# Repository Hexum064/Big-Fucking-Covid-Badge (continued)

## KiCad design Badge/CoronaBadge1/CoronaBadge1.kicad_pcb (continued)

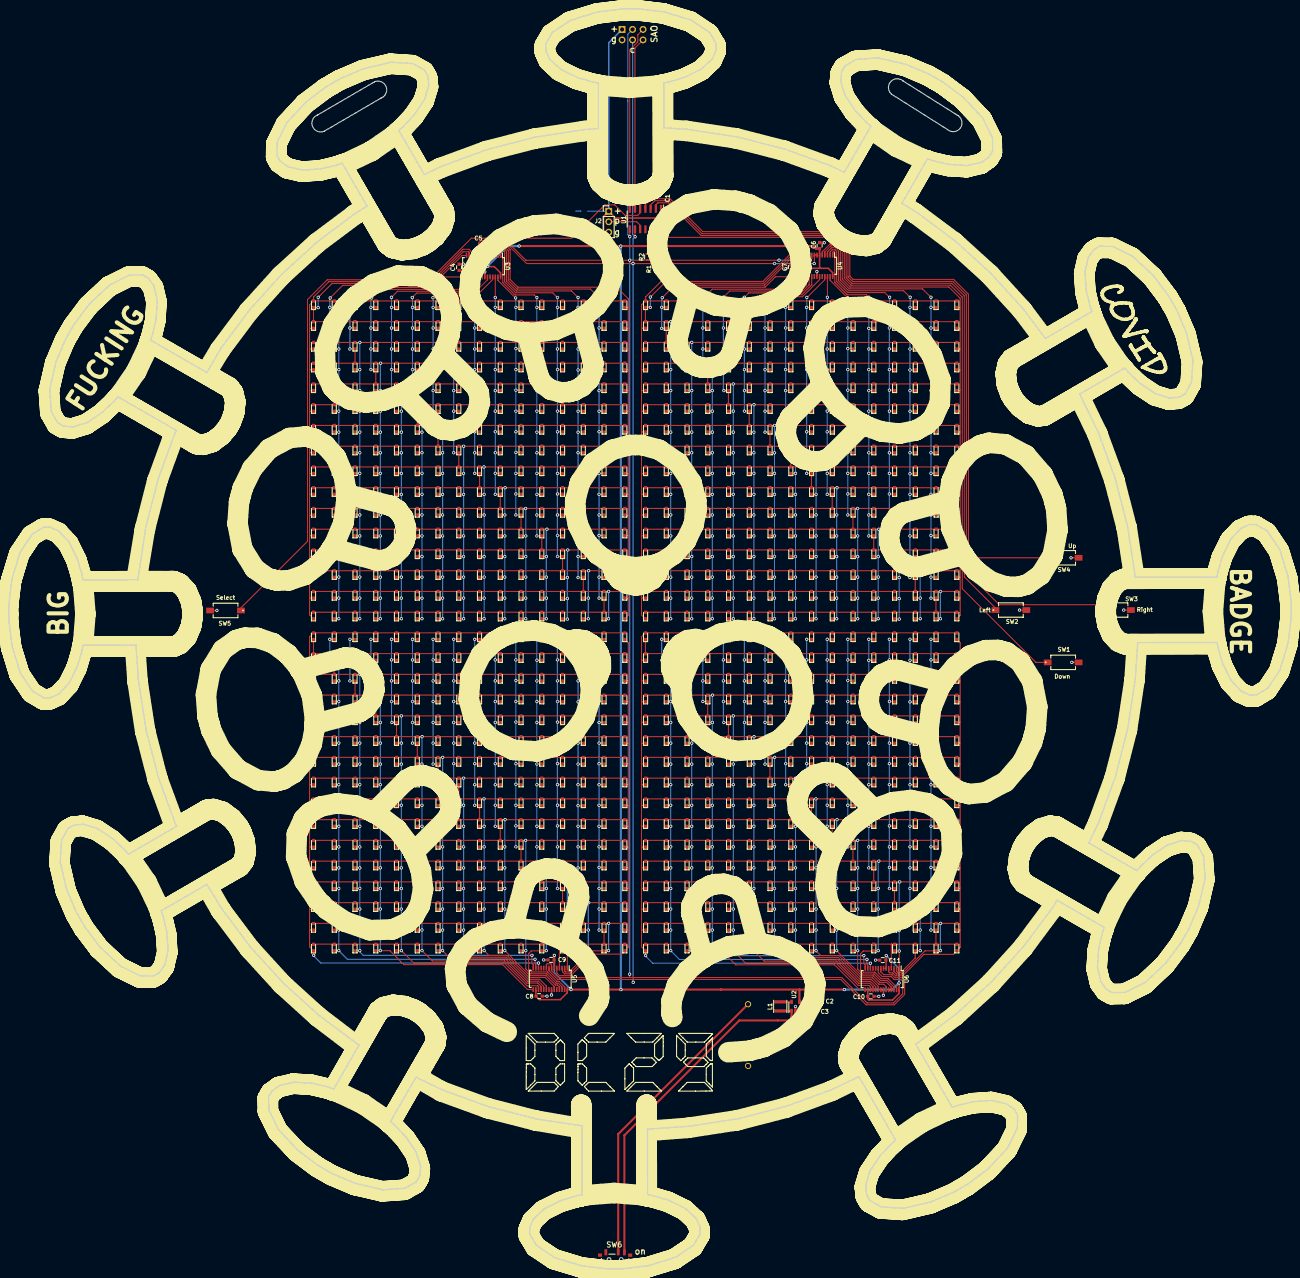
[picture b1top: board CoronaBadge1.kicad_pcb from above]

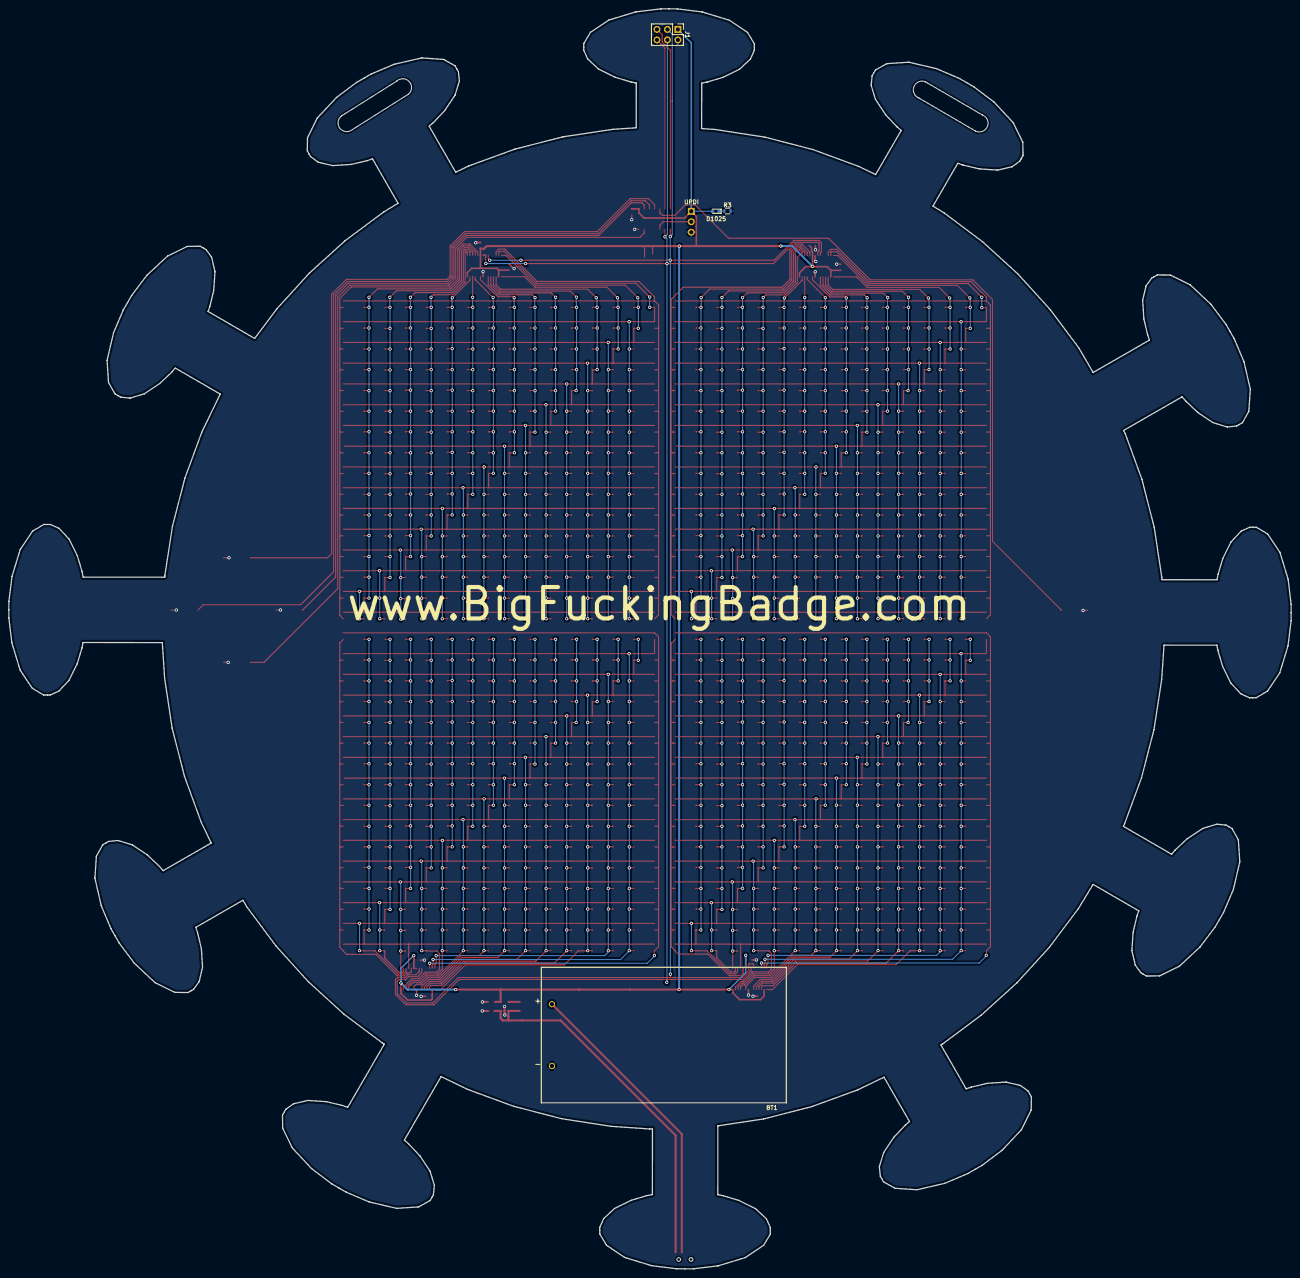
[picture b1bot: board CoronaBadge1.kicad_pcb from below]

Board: 2 copper layers, 311.4 x 306.0 mm, 1055 parts (4 on the bottom side), 84 nets.

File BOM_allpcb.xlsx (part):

*Ref Des | Manufacturer/Brand | *Mfg Part # | *Package | *Description / Value
D1 | https://lcsc.com/product-detail/Light-Emitting-Diodes-LED_XI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 | XL-1608SURC-06 | 0603 | 0603 SMT White LEDs
D2 | https://lcsc.com/product-detail/Light-Emitting-Diodes-LED_XI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 | XL-1608SURC-06 | 0603 | 0603 SMT White LEDs
D3 | https://lcsc.com/product-detail/Light-Emitting-Diodes-LED_XI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 | XL-1608SURC-06 | 0603 | 603 SMT White LEDs
D4 | https://lcsc.com/product-detail/Light-Emitting-Diodes-LED_XI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 | XL-1608SURC-06 | 0603 | 603 SMT White LEDs
D5 | https://lcsc.com/product-detail/Light-Emitting-Diodes-LED_XI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 | XL-1608SURC-06 | 0603 | 603 SMT White LEDs
D6 | https://lcsc.com/product-detail/Light-Emitting-Diodes-LED_XI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 | XL-1608SURC-06 | 0603 | 603 SMT White LEDs
D7 | https://lcsc.com/product-detail/Light-Emitting-Diodes-LED_XI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 | XL-1608SURC-06 | 0603 | 603 SMT White LEDs
D8 | https://lcsc.com/product-detail/Light-Emitting-Diodes-LED_XI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 | XL-1608SURC-06 | 0603 | 603 SMT White LEDs
D9 | https://lcsc.com/product-detail/Light-Emitting-Diodes-LED_XI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 | XL-1608SURC-06 | 0603 | 603 SMT White LEDs
D10 | https://lcsc.com/product-detail/Light-Emitting-Diodes-LED_XI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 | XL-1608SURC-06 | 0603 | 603 SMT White LEDs
D11 | https://lcsc.com/product-detail/Light-Emitting-Diodes-LED_XI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 | XL-1608SURC-06 | 0603 | 603 SMT White LEDs
D12 | https://lcsc.com/product-detail/Light-Emitting-Diodes-LED_XI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 | XL-1608SURC-06 | 0603 | 603 SMT White LEDs
D13 | https://lcsc.com/product-detail/Light-Emitting-Diodes-LED_XI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 | XL-1608SURC-06 | 0603 | 603 SMT White LEDs
D14 | https://lcsc.com/product-detail/Light-Emitting-Diodes-LED_XI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 | XL-1608SURC-06 | 0603 | 603 SMT White LEDs
D15 | https://lcsc.com/product-detail/Light-Emitting-Diodes-LED_XI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 | XL-1608SURC-06 | 0603 | 603 SMT White LEDs
D16 | https://lcsc.com/product-detail/Light-Emitting-Diodes-LED_XI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 | XL-1608SURC-06 | 0603 | 603 SMT White LEDs
D17 | https://lcsc.com/product-detail/Light-Emitting-Diodes-LED_XI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 | XL-1608SURC-06 | 0603 | 603 SMT White LEDs
D18 | https://lcsc.com/product-detail/Light-Emitting-Diodes-LED_XI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 | XL-1608SURC-06 | 0603 | 603 SMT White LEDs
D19 | https://lcsc.com/product-detail/Light-Emitting-Diodes-LED_XI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 | XL-1608SURC-06 | 0603 | 603 SMT White LEDs
D20 | https://lcsc.com/product-detail/Light-Emitting-Diodes-LED_XI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 | XL-1608SURC-06 | 0603 | 603 SMT White LEDs
D21 | https://lcsc.com/product-detail/Light-Emitting-Diodes-LED_XI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 | XL-1608SURC-06 | 0603 | 603 SMT White LEDs
D22 | https://lcsc.com/product-detail/Light-Emitting-Diodes-LED_XI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 | XL-1608SURC-06 | 0603 | 603 SMT White LEDs
D23 | https://lcsc.com/product-detail/Light-Emitting-Diodes-LED_XI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 | XL-1608SURC-06 | 0603 | 603 SMT White LEDs
D24 | https://lcsc.com/product-detail/Light-Emitting-Diodes-LED_XI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 | XL-1608SURC-06 | 0603 | 603 SMT White LEDs
D25 | https://lcsc.com/product-detail/Light-Emitting-Diodes-LED_XI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 | XL-1608SURC-06 | 0603 | 603 SMT White LEDs
D26 | https://lcsc.com/product-detail/Light-Emitting-Diodes-LED_XI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 | XL-1608SURC-06 | 0603 | 603 SMT White LEDs
D27 | https://lcsc.com/product-detail/Light-Emitting-Diodes-LED_XI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 | XL-1608SURC-06 | 0603 | 603 SMT White LEDs
D28 | https://lcsc.com/product-detail/Light-Emitting-Diodes-LED_XI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 | XL-1608SURC-06 | 0603 | 603 SMT White LEDs
D29 | https://lcsc.com/product-detail/Light-Emitting-Diodes-LED_XI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 | XL-1608SURC-06 | 0603 | 603 SMT White LEDs
D30 | https://lcsc.com/product-detail/Light-Emitting-Diodes-LED_XI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 | XL-1608SURC-06 | 0603 | 603 SMT White LEDs
D31 | https://lcsc.com/product-detail/Light-Emitting-Diodes-LED_XI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 | XL-1608SURC-06 | 0603 | 603 SMT White LEDs
D32 | https://lcsc.com/product-detail/Light-Emitting-Diodes-LED_XI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 | XL-1608SURC-06 | 0603 | 603 SMT White LEDs
D33 | https://lcsc.com/product-detail/Light-Emitting-Diodes-LED_XI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 | XL-1608SURC-06 | 0603 | 603 SMT White LEDs
D34 | https://lcsc.com/product-detail/Light-Emitting-Diodes-LED_XI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 | XL-1608SURC-06 | 0603 | 603 SMT White LEDs
D35 | https://lcsc.com/product-detail/Light-Emitting-Diodes-LED_XI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 | XL-1608SURC-06 | 0603 | 603 SMT White LEDs
D36 | https://lcsc.com/product-detail/Light-Emitting-Diodes-LED_XI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 | XL-1608SURC-06 | 0603 | 603 SMT White LEDs
D37 | https://lcsc.com/product-detail/Light-Emitting-Diodes-LED_XI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 | XL-1608SURC-06 | 0603 | 603 SMT White LEDs
D38 | https://lcsc.com/product-detail/Light-Emitting-Diodes-LED_XI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 | XL-1608SURC-06 | 0603 | 603 SMT White LEDs
D39 | https://lcsc.com/product-detail/Light-Emitting-Diodes-LED_XI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 | XL-1608SURC-06 | 0603 | 603 SMT White LEDs
D40 | https://lcsc.com/product-detail/Light-Emitting-Diodes-LED_XI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 | XL-1608SURC-06 | 0603 | 603 SMT White LEDs
D41 | https://lcsc.com/product-detail/Light-Emitting-Diodes-LED_XI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 | XL-1608SURC-06 | 0603 | 603 SMT White LEDs
D42 | https://lcsc.com/product-detail/Light-Emitting-Diodes-LED_XI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 | XL-1608SURC-06 | 0603 | 603 SMT White LEDs
D43 | https://lcsc.com/product-detail/Light-Emitting-Diodes-LED_XI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 | XL-1608SURC-06 | 0603 | 603 SMT White LEDs
D44 | https://lcsc.com/product-detail/Light-Emitting-Diodes-LED_XI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 | XL-1608SURC-06 | 0603 | 603 SMT White LEDs
D45 | https://lcsc.com/product-detail/Light-Emitting-Diodes-LED_XI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 | XL-1608SURC-06 | 0603 | 603 SMT White LEDs
D46 | https://lcsc.com/product-detail/Light-Emitting-Diodes-LED_XI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 | XL-1608SURC-06 | 0603 | 603 SMT White LEDs
D47 | https://lcsc.com/product-detail/Light-Emitting-Diodes-LED_XI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 | XL-1608SURC-06 | 0603 | 603 SMT White LEDs
D48 | https://lcsc.com/product-detail/Light-Emitting-Diodes-LED_XI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 | XL-1608SURC-06 | 0603 | 603 SMT White LEDs
D49 | https://lcsc.com/product-detail/Light-Emitting-Diodes-LED_XI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 | XL-1608SURC-06 | 0603 | 603 SMT White LEDs
D50 | https://lcsc.com/product-detail/Light-Emitting-Diodes-LED_XI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 | XL-1608SURC-06 | 0603 | 603 SMT White LEDs
D51 | https://lcsc.com/product-detail/Light-Emitting-Diodes-LED_XI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 | XL-1608SURC-06 | 0603 | 603 SMT White LEDs
D52 | https://lcsc.com/product-detail/Light-Emitting-Diodes-LED_XI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 | XL-1608SURC-06 | 0603 | 603 SMT White LEDs
D53 | https://lcsc.com/product-detail/Light-Emitting-Diodes-LED_XI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 | XL-1608SURC-06 | 0603 | 603 SMT White LEDs
D54 | https://lcsc.com/product-detail/Light-Emitting-Diodes-LED_XI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 | XL-1608SURC-06 | 0603 | 603 SMT White LEDs
D55 | https://lcsc.com/product-detail/Light-Emitting-Diodes-LED_XI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 | XL-1608SURC-06 | 0603 | 603 SMT White LEDs
D56 | https://lcsc.com/product-detail/Light-Emitting-Diodes-LED_XI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 | XL-1608SURC-06 | 0603 | 603 SMT White LEDs
D57 | https://lcsc.com/product-detail/Light-Emitting-Diodes-LED_XI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 | XL-1608SURC-06 | 0603 | 603 SMT White LEDs
D58 | https://lcsc.com/product-detail/Light-Emitting-Diodes-LED_XI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 | XL-1608SURC-06 | 0603 | 603 SMT White LEDs
D59 | https://lcsc.com/product-detail/Light-Emitting-Diodes-LED_XI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 | XL-1608SURC-06 | 0603 | 603 SMT White LEDs
D60 | https://lcsc.com/product-detail/Light-Emitting-Diodes-LED_XI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 | XL-1608SURC-06 | 0603 | 603 SMT White LEDs
D61 | https://lcsc.com/product-detail/Light-Emitting-Diodes-LED_XI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 | XL-1608SURC-06 | 0603 | 603 SMT White LEDs
D62 | https://lcsc.com/product-detail/Light-Emitting-Diodes-LED_XI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 | XL-1608SURC-06 | 0603 | 603 SMT White LEDs
D63 | https://lcsc.com/product-detail/Light-Emitting-Diodes-LED_XI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 | XL-1608SURC-06 | 0603 | 603 SMT White LEDs
D64 | https://lcsc.com/product-detail/Light-Emitting-Diodes-LED_XI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 | XL-1608SURC-06 | 0603 | 603 SMT White LEDs
D65 | https://lcsc.com/product-detail/Light-Emitting-Diodes-LED_XI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 | XL-1608SURC-06 | 0603 | 603 SMT White LEDs
D66 | https://lcsc.com/product-detail/Light-Emitting-Diodes-LED_XI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 | XL-1608SURC-06 | 0603 | 603 SMT White LEDs
D67 | https://lcsc.com/product-detail/Light-Emitting-Diodes-LED_XI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 | XL-1608SURC-06 | 0603 | 603 SMT White LEDs
D68 | https://lcsc.com/product-detail/Light-Emitting-Diodes-LED_XI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 | XL-1608SURC-06 | 0603 | 603 SMT White LEDs
D69 | https://lcsc.com/product-detail/Light-Emitting-Diodes-LED_XI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 | XL-1608SURC-06 | 0603 | 603 SMT White LEDs
D70 | https://lcsc.com/product-detail/Light-Emitting-Diodes-LED_XI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 | XL-1608SURC-06 | 0603 | 603 SMT White LEDs
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
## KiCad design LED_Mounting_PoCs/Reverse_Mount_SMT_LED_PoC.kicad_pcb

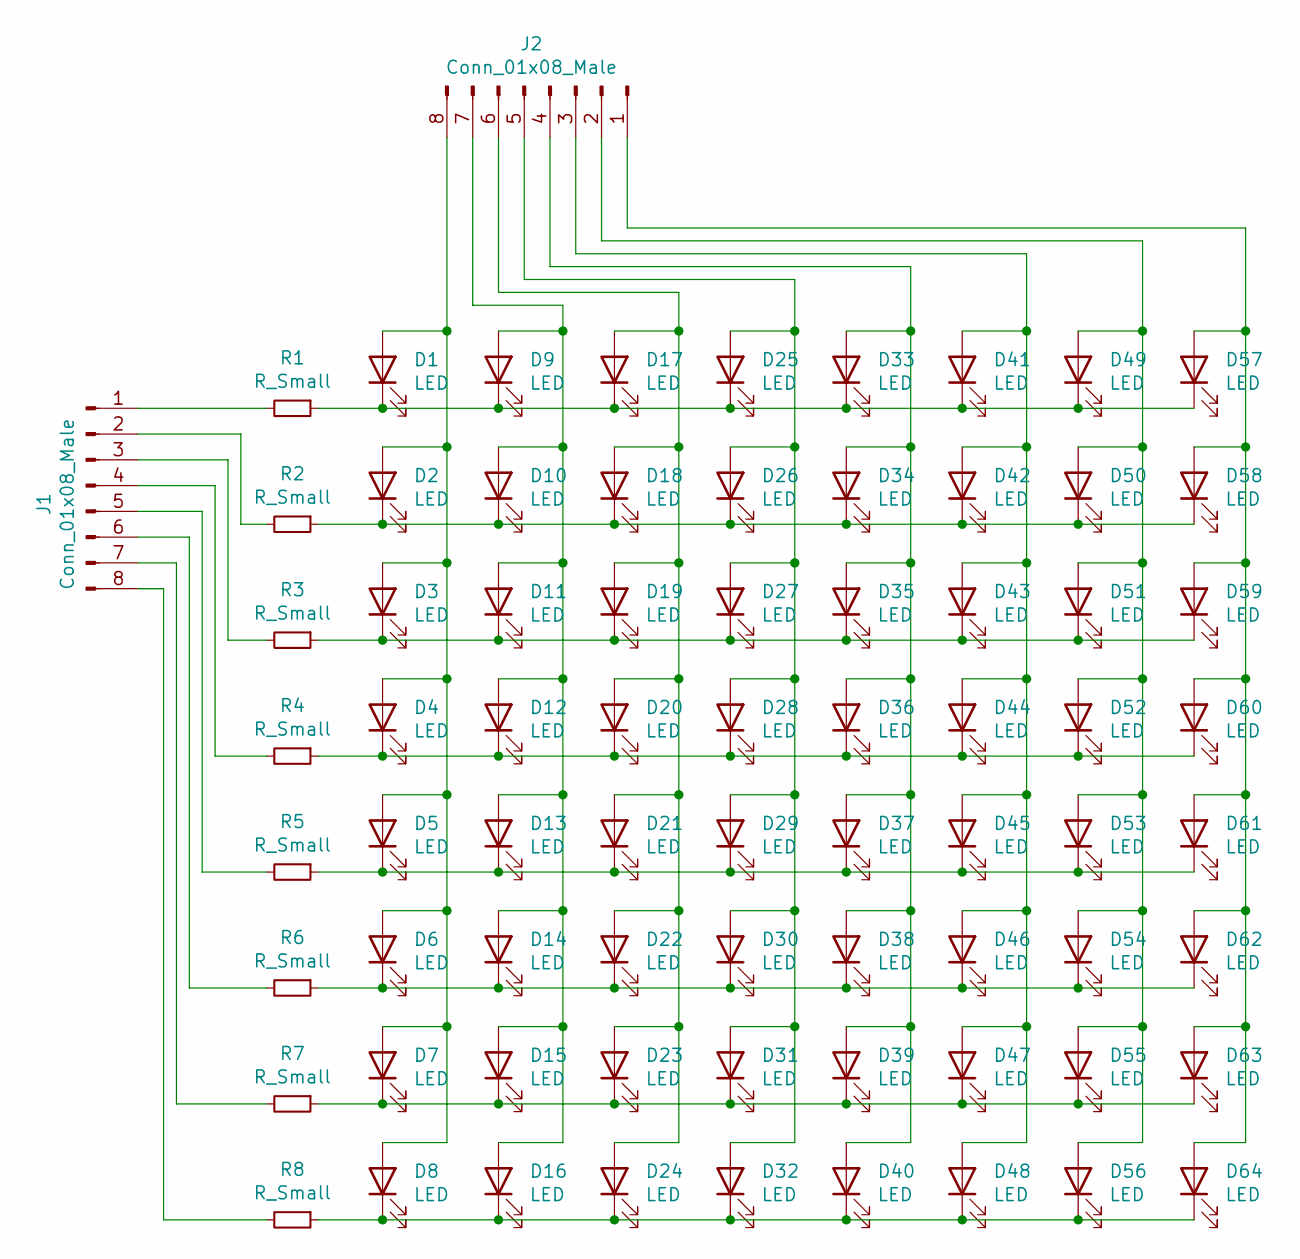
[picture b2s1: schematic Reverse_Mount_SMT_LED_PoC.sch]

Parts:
D1, D2, D3, D4, D5, D6, D7, D8, D9, D10, D11, D12, D13, D14, D15, D16, D17, D18, D19, D20, D21, D22, D23, D24, D25, D26, D27, D28, D29, D30, D31, D32, D33, D34, D35, D36, D37, D38, D39, D40, D41, D42, D43, D44, D45, D46, D47, D48, D49, D50, D51, D52, D53, D54, D55, D56, D57, D58, D59, D60, D61, D62, D63, D64: LED; 0603_LED_Reverse
J1, J2: Conn_01x08_Male; Pin_Header_Straight_1x08_Pitch2.54mm
R1, R2, R3, R4, R5, R6, R7, R8: R_Small; R_0603

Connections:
unnamed: D1.1 (K), D9.1 (K), D17.1 (K), D25.1 (K), D33.1 (K), D41.1 (K), D49.1 (K), D57.1 (K), R1.1
unnamed: D1.2 (A), D2.2 (A), D3.2 (A), D4.2 (A), D5.2 (A), D6.2 (A), D7.2 (A), D8.2 (A), J2.8
unnamed: D2.1 (K), D10.1 (K), D18.1 (K), D26.1 (K), D34.1 (K), D42.1 (K), D50.1 (K), D58.1 (K), R2.1
unnamed: D9.2 (A), D10.2 (A), D11.2 (A), D12.2 (A), D13.2 (A), D14.2 (A), D15.2 (A), D16.2 (A), J2.7
unnamed: D3.1 (K), D11.1 (K), D19.1 (K), D27.1 (K), D35.1 (K), D43.1 (K), D51.1 (K), D59.1 (K), R3.1
unnamed: D4.1 (K), D12.1 (K), D20.1 (K), D28.1 (K), D36.1 (K), D44.1 (K), D52.1 (K), D60.1 (K), R4.1
unnamed: D5.1 (K), D13.1 (K), D21.1 (K), D29.1 (K), D37.1 (K), D45.1 (K), D53.1 (K), D61.1 (K), R5.1
unnamed: D6.1 (K), D14.1 (K), D22.1 (K), D30.1 (K), D38.1 (K), D46.1 (K), D54.1 (K), D62.1 (K), R6.1
unnamed: D7.1 (K), D15.1 (K), D23.1 (K), D31.1 (K), D39.1 (K), D47.1 (K), D55.1 (K), D63.1 (K), R7.1
unnamed: D8.1 (K), D16.1 (K), D24.1 (K), D32.1 (K), D40.1 (K), D48.1 (K), D56.1 (K), D64.1 (K), R8.1
unnamed: D17.2 (A), D18.2 (A), D19.2 (A), D20.2 (A), D21.2 (A), D22.2 (A), D23.2 (A), D24.2 (A), J2.6
unnamed: D25.2 (A), D26.2 (A), D27.2 (A), D28.2 (A), D29.2 (A), D30.2 (A), D31.2 (A), D32.2 (A), J2.5
unnamed: D33.2 (A), D34.2 (A), D35.2 (A), D36.2 (A), D37.2 (A), D38.2 (A), D39.2 (A), D40.2 (A), J2.4
unnamed: D41.2 (A), D42.2 (A), D43.2 (A), D44.2 (A), D45.2 (A), D46.2 (A), D47.2 (A), D48.2 (A), J2.3
unnamed: D49.2 (A), D50.2 (A), D51.2 (A), D52.2 (A), D53.2 (A), D54.2 (A), D55.2 (A), D56.2 (A), J2.2
unnamed: D57.2 (A), D58.2 (A), D59.2 (A), D60.2 (A), D61.2 (A), D62.2 (A), D63.2 (A), D64.2 (A), J2.1
unnamed: J1.1, R1.2
unnamed: J1.2, R2.2
unnamed: J1.3, R3.2
unnamed: J1.4, R4.2
unnamed: J1.5, R5.2
unnamed: J1.6, R6.2
unnamed: J1.7, R7.2
unnamed: J1.8, R8.2

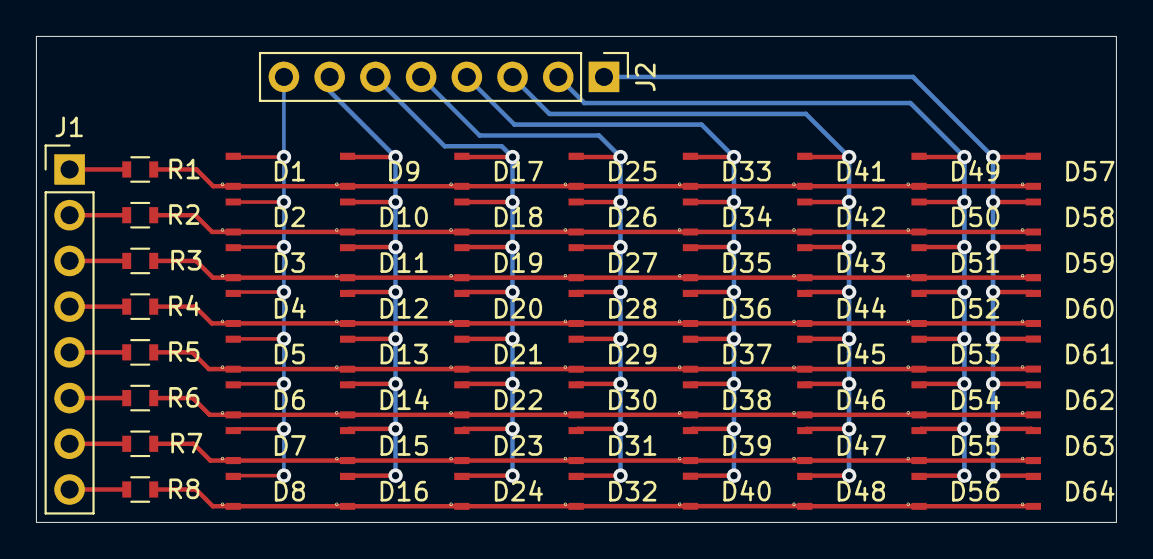
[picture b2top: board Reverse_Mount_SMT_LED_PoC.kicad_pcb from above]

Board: 2 copper layers, 60.0 x 27.0 mm, 74 parts (0 on the bottom side), 24 nets.

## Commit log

2021-06-16 Added 64 and 256 led layouts
2021-07-26 finished
